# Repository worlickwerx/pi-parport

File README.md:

## pi-parport

This is a Raspberry Pi HAT that implements a PC-style parallel port.
GPIO pins are organized as data, status, and control registers.
The HAT includes a buffer chip that converts from the GPIB 3V3 logic
to signals that conform to IEEE 1284.  A 26 pin IDC header on the
board connects to your DB25 connector.  A `parport-gpio` driver and
device tree overlay integrate the HAT with the Linux parport driver stack.

### Why?

I wanted to use a parallel port based cooled astronomy camera,
but preferred to use the compact and low-power Raspberry Pi
over a PC at the telescope.  Parallel ports are simple devices.
Why not build one?

### What works?

See [wiki](https://github.com/worlickwerx/pi-parport/wiki) for notes on some
devices, and please share your experience if you try something new.

The following limitations of this implementation may affect software and
hardware that uses the parallel port:
1) The software cannot directly read and write the x86 port addresses,
as was the custom early on.  In user space, software must use the ppdev
ioctl interface.  In the kernel, software must use the (generic)
`struct parport` operations.
2) The GPIO multiplexing/de-multiplexing and/or system call access may
impact the direct-access latency assumed by some bit-banged drivers.
On a Pi 3, user space code can toggle a parallel port line at about 250 kHz.
3) Bidirectional control pins are not currently supported, but bidirectional
data pins are supported.  There are alternatives to the current buffer chip
that would support this, but they require a slightly more complicated
circuit.

### Why not use a USB Parallel Port?

Many USB parallel port devices appear to Linux as a USB printer, bypassing
the parport driver stack.  If your application is a printer, go for it.

### Building the driver

For convenience, the generic parport code is duplicated in this repo,
since the Raspberry Pi Foundation does not ship the compiled modules
in the `raspberrypi-kernel` package (at least in old Raspbian
versions).  If you are intending to use a specific old version of
Raspbian, there is the shell script `get_parport_src.sh` to assist
you in getting the code from that particular version.

Clone this repo, then run the following with `${TOPDIR}` representing the
top level directory of the cloned repo:
```console
$ sudo apt install build-essential raspberrypi-kernel-headers
$ cd ${TOPDIR}/driver
$ make
make -C /lib/modules/4.19.75-v7+/build M=${TOPDIR}/driver modules
make[1]: Entering directory '/usr/src/linux-headers-4.19.75-v7+'
  CC [M]  ${TOPDIR}/driver/parport/share.o
  CC [M]  ${TOPDIR}/driver/parport/ieee1284.o
  CC [M]  ${TOPDIR}/driver/parport/ieee1284_ops.o
  CC [M]  ${TOPDIR}/driver/parport/procfs.o
  CC [M]  ${TOPDIR}/driver/parport/daisy.o
  CC [M]  ${TOPDIR}/driver/parport/probe.o
  LD [M]  ${TOPDIR}/driver/parport/parport.o
  CC [M]  ${TOPDIR}/driver/parport/lp.o
  CC [M]  ${TOPDIR}/driver/parport/ppdev.o
  CC [M]  ${TOPDIR}/driver/parport_gpio.o
  Building modules, stage 2.
  MODPOST 4 modules
  CC      ${TOPDIR}/driver/parport/lp.mod.o
  LD [M]  ${TOPDIR}/driver/parport/lp.ko
  CC      ${TOPDIR}/driver/parport/parport.mod.o
  LD [M]  ${TOPDIR}/driver/parport/parport.ko
  CC      ${TOPDIR}/driver/parport/ppdev.mod.o
  LD [M]  ${TOPDIR}/driver/parport/ppdev.ko
  CC      ${TOPDIR}/driver/parport_gpio.mod.o
  LD [M]  ${TOPDIR}/driver/parport_gpio.ko
make[1]: Leaving directory '/usr/src/linux-headers-4.19.75-v7+'
```

### Installing the Device Tree Overlay

The device tree overlay maps specific GPIO pins to their functions in
the driver.  This must be compiled and loaded:
```console
$ cd ${TOPDIR}/dts
$ make
$ sudo make install
```
The ID EEPROM stores the name of the DT Overlay to use, and the
corresponding DT Overlay will be automatically loaded on boot.  If you
will not be using an ID EEPROM, then add the following line to
`/boot/config.txt`:
```
dtoverlay=parport-gpio
```
The default drive mode of the parallel port output pins is
"totem-pole" mode, which means that a high current source is provided
for both logic level 1 and 0.  If you wish logic level 1 to be a low
current source provided by pull-up resistors, i.e. "open-drain" mode,
then you can set the following DT Overlay parameter:
```
dtoverlay=parport-gpio,hd=0
```
Note that if you are using an EEPROM, you will have to include the
full DT Overlay data within your EEPROM since you cannot simply
specify a parameter when loading by that method.

Then reboot the pi to pick up the new config.

### Installing the Modules

Install the modules to allow Linux Device Tree to automatically load
them.
```console
$ cd ${TOPDIR}/driver
$ sudo make install
```
Note that only the `parport` and `parport_gpio` base modules will
autoload, the `ppdev` and `lp` modules will still need to be specified
in `/etc/modules` or otherwise.  Also, note that you will need to
rebuild and reinstall the modules when you update your kernel version.

### Loading the Modules

If you did not install the modules, after rebooting, load the base
modules like this:
```console
$ cd ${TOPDIR}
$ sudo insmod driver/parport/parport.ko
$ sudo insmod driver/parport_gpio.ko
```
You'll see the port announce itself on the console:
```console
[4425200.988400] parport-gpio ppgpio@0: data on pins [22,23,24,10,25,9,8,11]
[4425200.988412] parport-gpio ppgpio@0: status on pins [18,17,4,3,2]
[4425200.988422] parport-gpio ppgpio@0: control on pins [26,19,6,13]
[4425200.988430] parport-gpio ppgpio@0: hd on pin 20
[4425200.988438] parport-gpio ppgpio@0: dir on pin 21
```
If you wish to set up a parallel printer:
```console
$ sudo insmod parport/lp.ko
```
If you wish to run user-space programs that use the parallel port:
```console
$ sudo insmod parport/ppdev.ko
```

### hardware

The latest hardware includes an ID EEPROM to conform with the
[Raspberry Pi HAT Specification](https://github.com/raspberrypi/hats),
and was designed with [KiCAD](https://www.kicad.org/).
As with the previous versions, the
[SN74LVC161284 19-bit bus interface with 3-state outputs](http://www.ti.com/product/SN74LVC161284) takes care of buffering and line conditioning.

Version 4 is shared on
[OSHPARK](https://oshpark.com/shared_projects/0Ioh20Gk).
See the [Bill of Materials](hardware/v4/BOM.md) for parts to place on
the board.

Populating the EEPROM and associated components on a board you're making
yourself is optional.

Check out the [test](test/) directory for some simple "smoke tests"
on your assembled pi-parport board before attaching your more
expensive equipment.

Schematics and design files for [previous versions](hardware/)
are still available for reference.

### Release

Share and enjoy!

#### Software License

SPDX-License-Identifier: GPL-2.0-or-later

#### Hardware License

SPDX-License-Identifier: CERN-OHL-1.2

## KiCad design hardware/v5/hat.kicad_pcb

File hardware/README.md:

### v4 hardware

v4 mainly corrects some minor flaws in the v3 design.  Bypass
capacitors are added, a few traces are rerouted to avoid passing under
resistors, and the footprints for the EEPROM resistors are changed
from 0603 to 0805.  Also, a few CAD-related inconsistencies were
fixed, like unclosed board outline and footprints not being consistent
between the schematic and board layout files.

[Schematic](v4/pi-parport.pdf) and [Bill of Materials](v4/BOM.md).

### v3 hardware

v3 adds an EEPROM to be a proper HAT.  It also converts the design files 
from Eagle to KiCad as a step to making additional board variations and 
modifications more accessible.  Unfortunately, bypass capacitors were 
left out of the redesign.

This board is shared on [OSHPARK](https://oshpark.com/shared_projects/gevwv2YP).
See also:  [Schematic](v3/pi-parport.pdf) and [Bill of Materials](v3/BOM.md).

### v2 hardware

v2 addresses the line termination and data direction limitations of v1,
using a single, purpose-built chip, the
[SN74LVC161284 19-bit bus interface with 3-state outputs](http://www.ti.com/product/SN74LVC161284).

This board was designed with Eagle, and is shared on
[OSHPARK](https://oshpark.com/shared_projects/Padn3qhP).
See also: [Schematic](v2/schematic.pdf) and [Bill of Materials](v2/BOM.md).

It works!  However, it doesn't conform to the HAT specification because
of the lack of EEPROM, and the IDC connector footprint is for a vertical
connector, but right angle would have helped the Pi fit into smaller cases.
(RA works, but it hangs over the board edge).

### v1 hardware

Three
[74AHCT541 octal buffers/drivers with 3-state outputs](http://www.ti.com/product/SN74AHCT541)
chips convert to/from the Pi's 3V3 line level and the parallel port's 5V.

This board was designed with Eagle.  See also: [Schematic](v1/schematic.pdf).

This version worked for my intended application (SBIG parallel port camera),
but due to missing line termination, only with a very short cable.  This
design also does not implement bidirectional DATA.

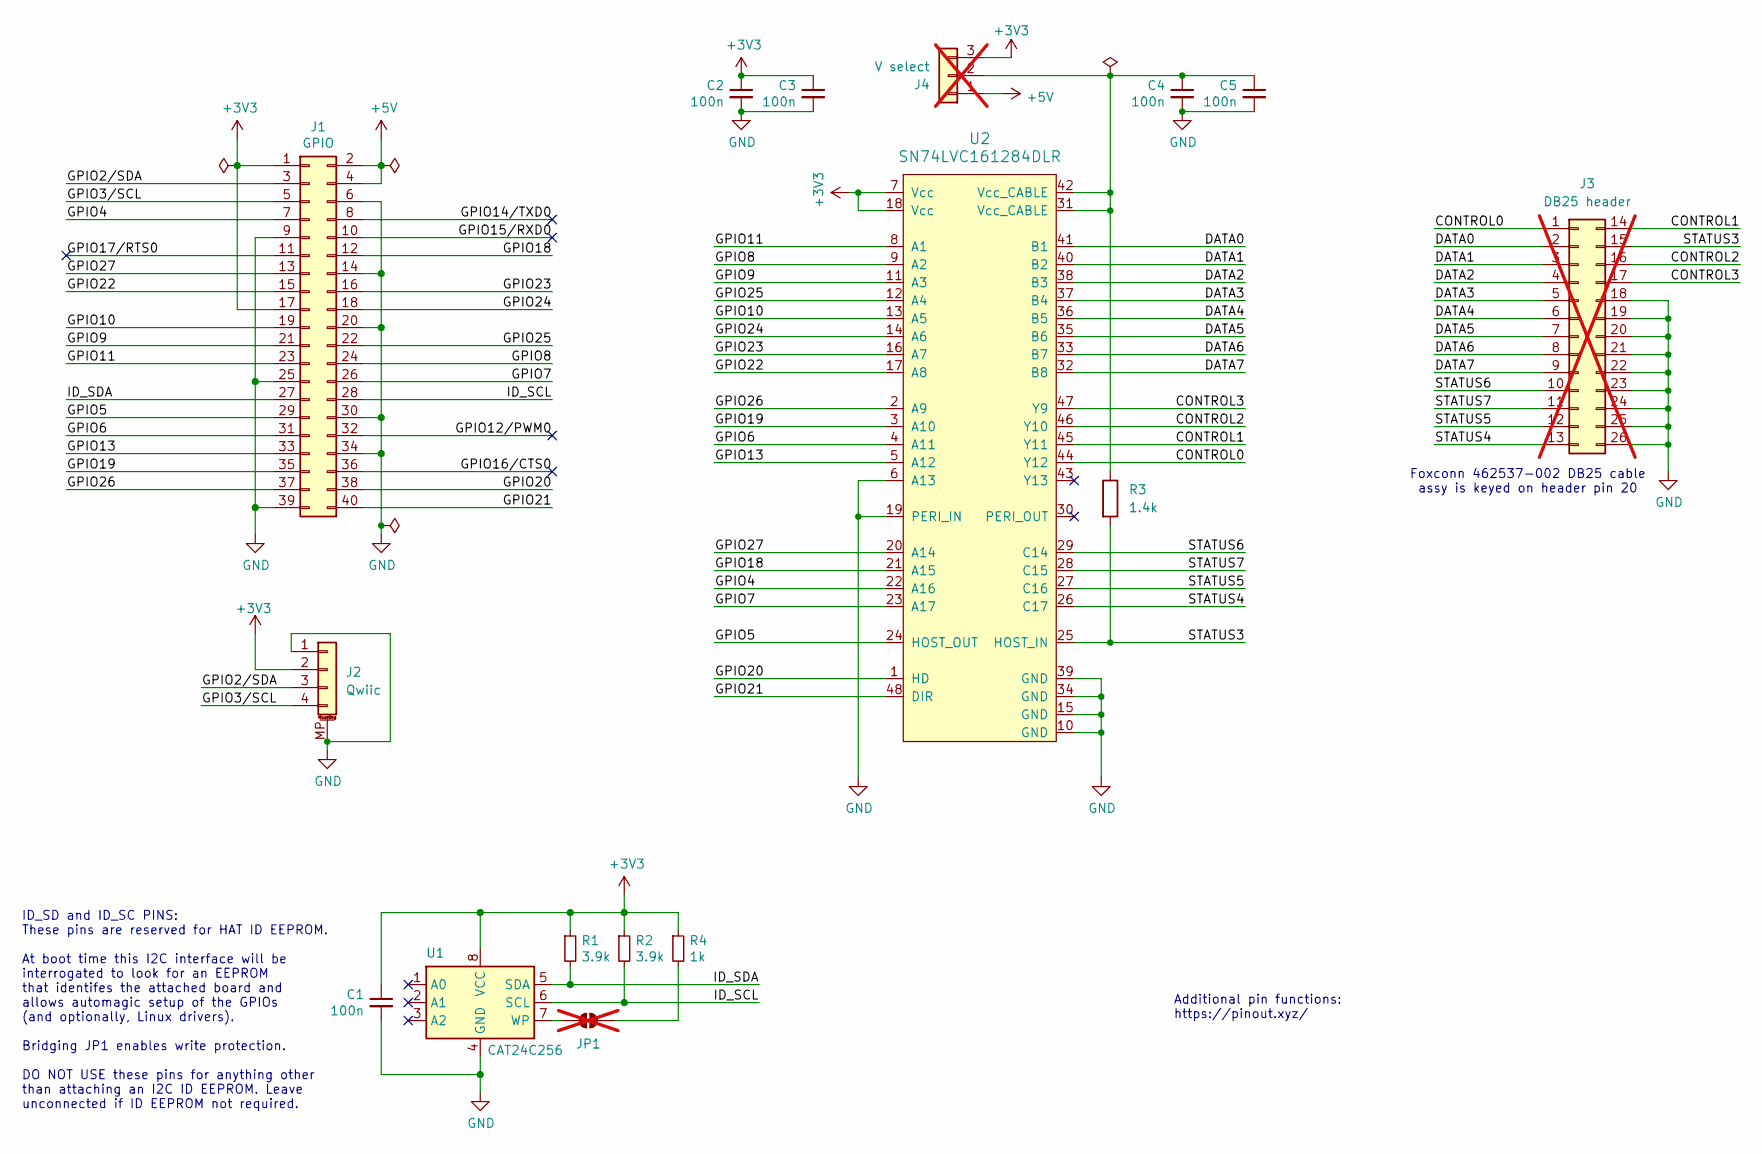
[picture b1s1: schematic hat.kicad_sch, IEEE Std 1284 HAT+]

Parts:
C1, C2, C3, C4, C5: 100n; C_0603_1608Metric; LCSC C346189
J1: GPIO; Harwin_M20-7812045_2x20_P2.54mm_Vertical; LCSC C2685112
J2: Qwiic; JST_SH_SM04B-SRSS-TB_1x04-1MP_P1.00mm_Horizontal; LCSC C2845363
J3: DB25 header; DB25_header_2x13_P2.54mm_horizontal; not fitted
J4: V select; PinHeader_1x03_P2.54mm_Vertical; not fitted
JP1: ID_WP; SolderJumper-2_P1.3mm_Open_RoundedPad1.0x1.5mm; not fitted
R1, R2: 3.9k; R_0603_1608Metric; LCSC C114616
R3: 1.4k; R_0603_1608Metric; LCSC C185359
R4: 1k; R_0603_1608Metric; LCSC C21190
U1: CAT24C256; SOIC-8_3.9x4.9mm_P1.27mm; LCSC C79987
U2: SN74LVC161284DLR; SSOP-48_7.5x15.9mm_P0.635mm; Mouser 595-SN74LVC161284DLR

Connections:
+3V3: C1.1, C2.1, C3.1, J1.1, J1.17, J2.2, J4.3, R1.1, R2.1, R4.1, U1.8 (VCC), U2.7 (Vcc), U2.18 (Vcc)
+5V: J1.2, J1.4, J4.1
/CONTROL0: J3.1, U2.44 (Y12)
/CONTROL1: J3.14, U2.45 (Y11)
/CONTROL2: J3.16, U2.46 (Y10)
/CONTROL3: J3.17, U2.47 (Y9)
/DATA0: J3.2, U2.41 (B1)
/DATA1: J3.3, U2.40 (B2)
/DATA2: J3.4, U2.38 (B3)
/DATA3: J3.5, U2.37 (B4)
/DATA4: J3.6, U2.36 (B5)
/DATA5: J3.7, U2.35 (B6)
/DATA6: J3.8, U2.33 (B7)
/DATA7: J3.9, U2.32 (B8)
/GPIO2/SDA: J1.3, J2.3
/GPIO3/SCL: J1.5, J2.4
/GPIO4: J1.7, U2.22 (A16)
/GPIO5: J1.29, U2.24 (HOST_OUT)
/GPIO6: J1.31, U2.4 (A11)
/GPIO7: J1.26, U2.23 (A17)
/GPIO8: J1.24, U2.9 (A2)
/GPIO9: J1.21, U2.11 (A3)
/GPIO10: J1.19, U2.13 (A5)
/GPIO11: J1.23, U2.8 (A1)
/GPIO12/PWM0: J1.32
/GPIO13: J1.33, U2.5 (A12)
/GPIO14/TXD0: J1.8
/GPIO15/RXD0: J1.10
/GPIO16/CTS0: J1.36
/GPIO17/RTS0: J1.11
/GPIO18: J1.12, U2.21 (A15)
/GPIO19: J1.35, U2.3 (A10)
/GPIO20: J1.38, U2.1 (HD)
/GPIO21: J1.40, U2.48 (DIR)
/GPIO22: J1.15, U2.17 (A8)
/GPIO23: J1.16, U2.16 (A7)
/GPIO24: J1.18, U2.14 (A6)
/GPIO25: J1.22, U2.12 (A4)
/GPIO26: J1.37, U2.2 (A9)
/GPIO27: J1.13, U2.20 (A14)
/ID_SCL: J1.28, R2.2, U1.6 (SCL)
/ID_SDA: J1.27, R1.2, U1.5 (SDA)
/STATUS3: J3.15, R3.2, U2.25 (HOST_IN)
/STATUS4: J3.13, U2.26 (C17)
/STATUS5: J3.12, U2.27 (C16)
/STATUS6: J3.10, U2.29 (C14)
/STATUS7: J3.11, U2.28 (C15)
GND: C1.2, C2.2, C3.2, C4.2, C5.2, J1.6, J1.9, J1.14, J1.20, J1.25, J1.30, J1.34, J1.39, J2.1, J2.MP (MountPin), J3.18, J3.19, J3.20, J3.21, J3.22, J3.23, J3.24, J3.25, J3.26, U1.4 (GND), U2.6 (A13), U2.10 (GND), U2.15 (GND), U2.19 (PERI_IN), U2.34 (GND), U2.39 (GND)
unnamed: C4.1, C5.1, J4.2, R3.1, U2.31 (Vcc_CABLE), U2.42 (Vcc_CABLE)
unnamed: JP1.1 (A), U1.7 (WP)
unnamed: JP1.2 (B), R4.2

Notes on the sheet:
Additional pin functions: https://pinout.xyz/
ID_SD and ID_SC PINS: These pins are reserved for HAT ID EEPROM. At boot time this I2C interface will be interrogated to look for an EEPROM that identifes the attached board and allows automagic setup of the GPIOs (and optionally, Linux drivers). Bridging JP1 enables write protection. DO NOT USE th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
Foxconn 462537-002 DB25 cable assy is keyed on header pin 20

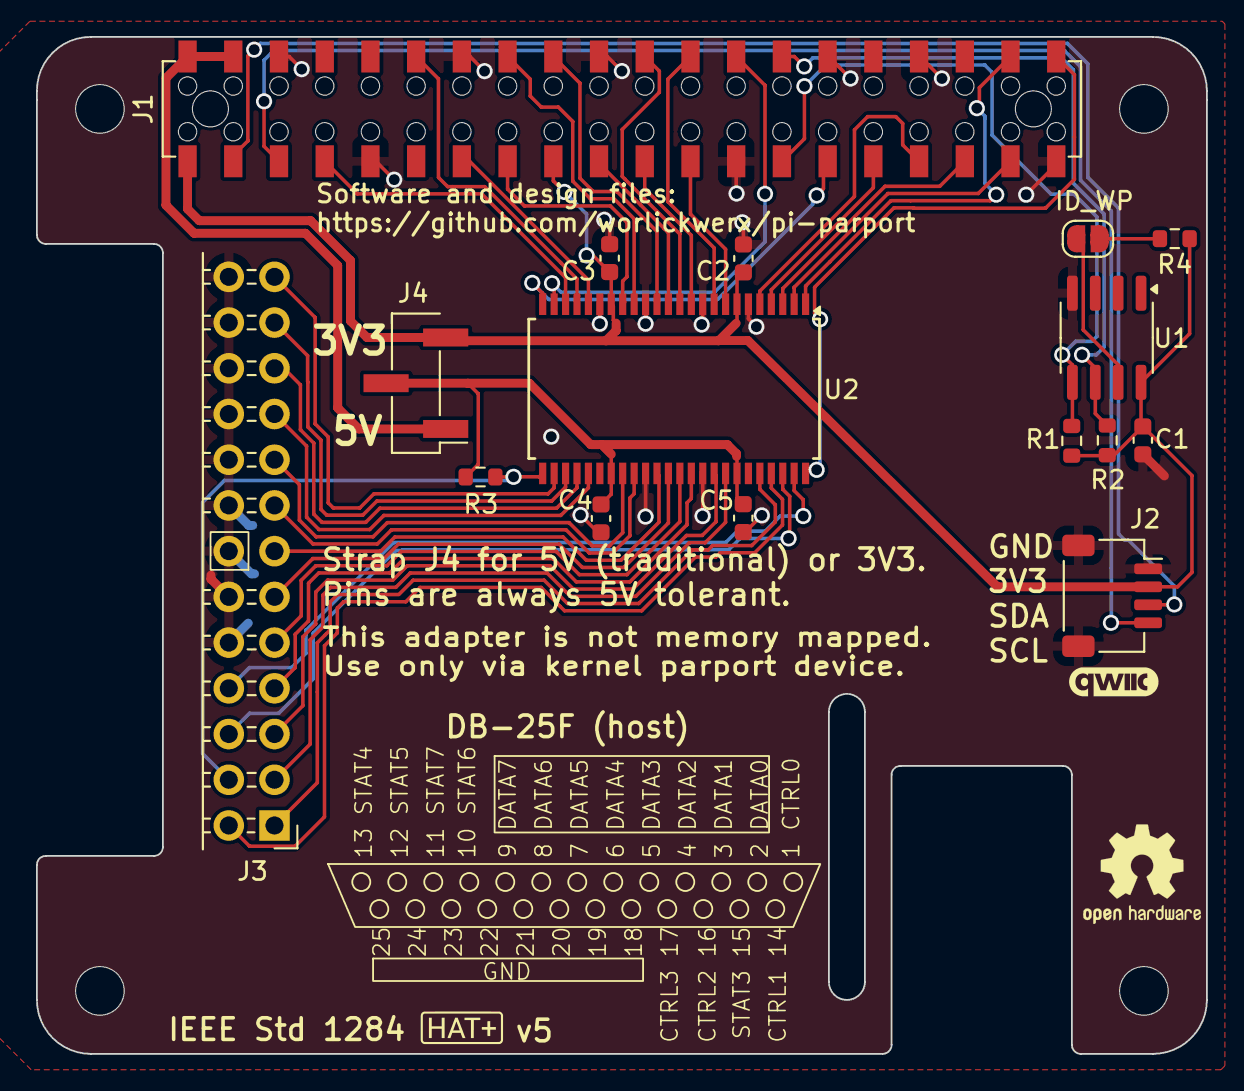
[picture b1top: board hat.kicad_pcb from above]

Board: 2 copper layers, 65.0 x 56.5 mm, 20 parts (0 on the bottom side), 46 nets.

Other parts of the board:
MH1, MH2, MH3, MH4: MountingHole_2.7mm_M2.5

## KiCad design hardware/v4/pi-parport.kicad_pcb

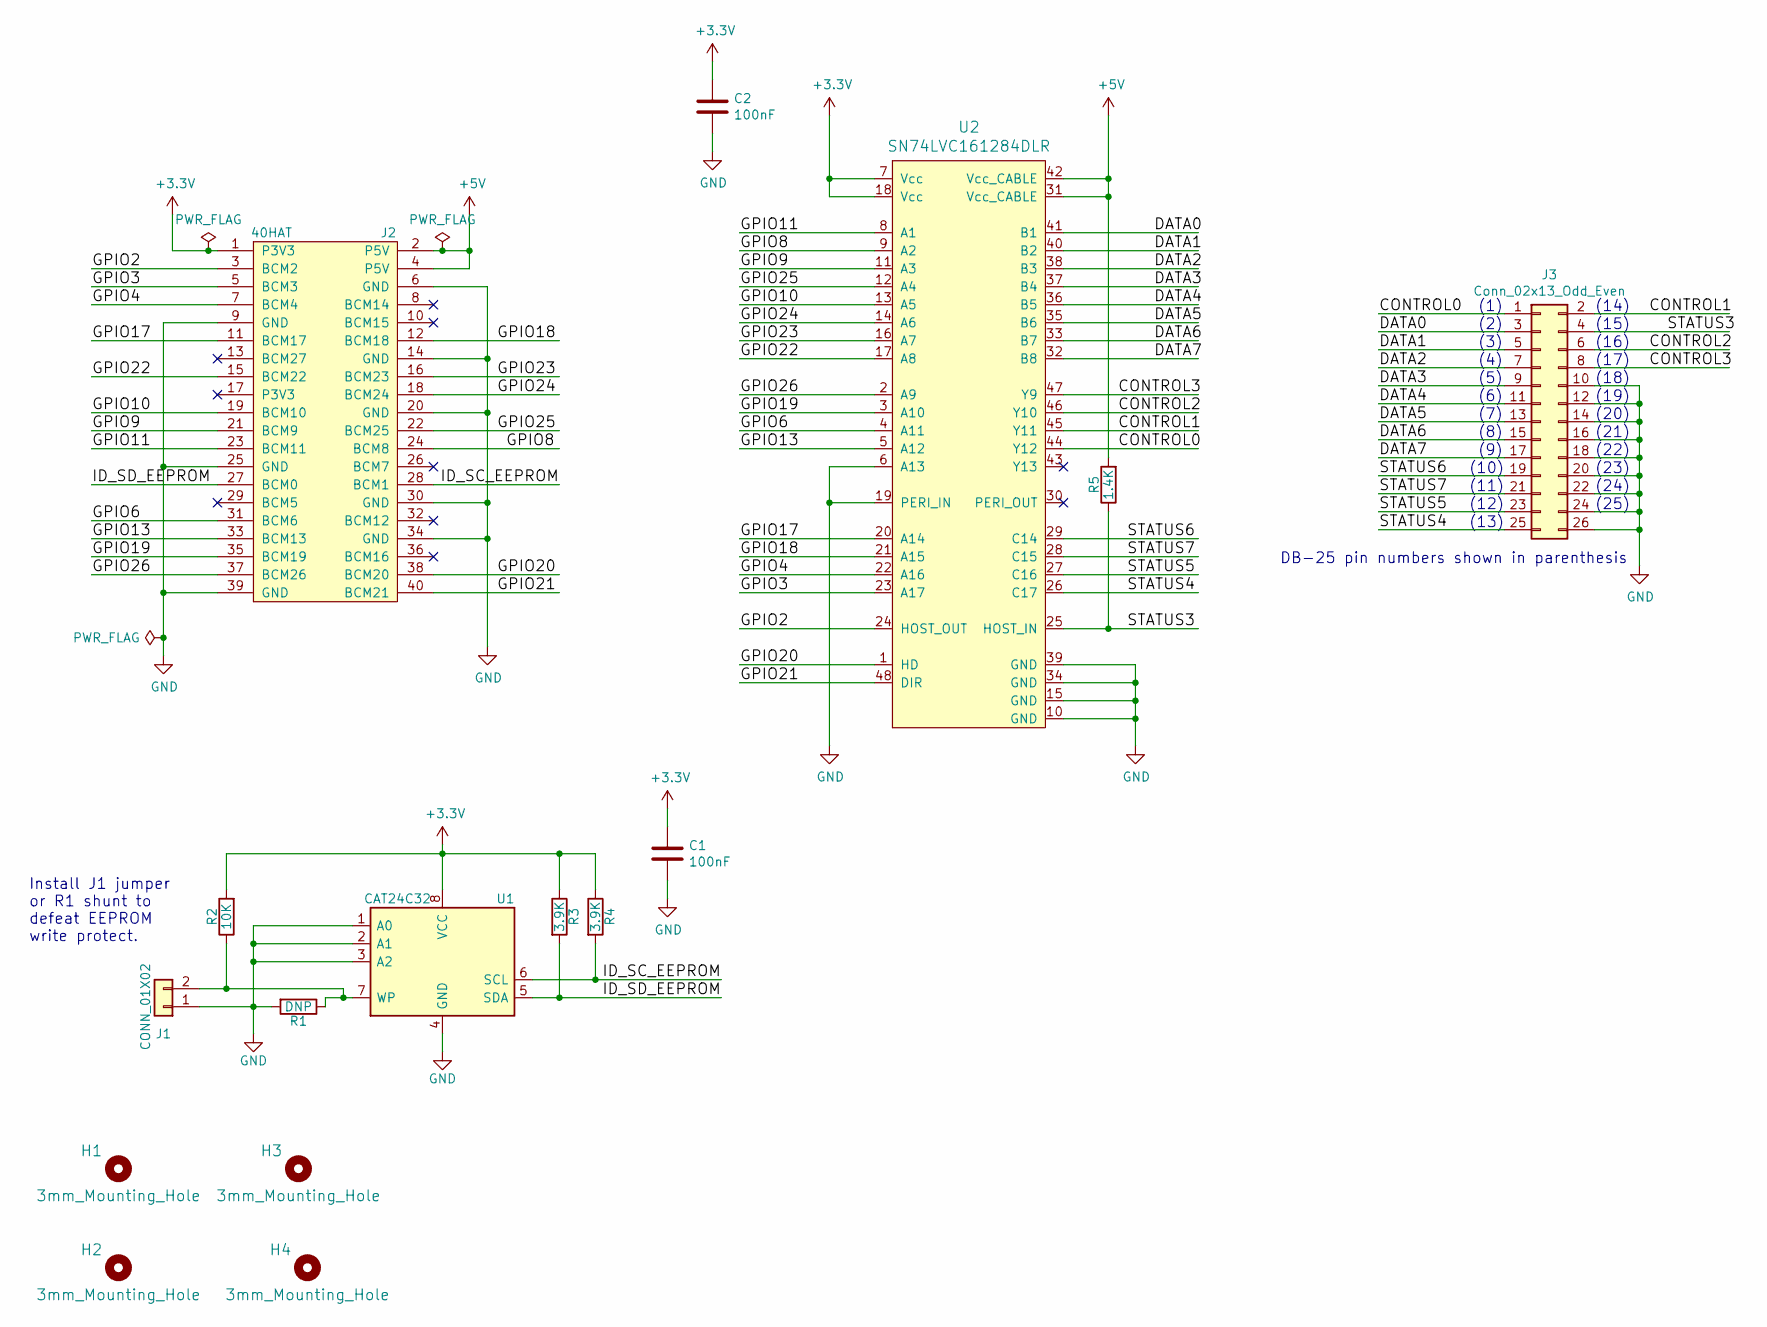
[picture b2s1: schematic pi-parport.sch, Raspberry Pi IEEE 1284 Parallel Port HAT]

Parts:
C1, C2: 100nF; C_0805_2012Metric_Pad1.15x1.40mm_HandSolder; MPN C0805C104Z5VACTU; Digi-Key_PN 399-1177-1-ND
H1, H2, H3, H4: 3mm_Mounting_Hole; NPTH_3mm_ID
J1: CONN_01X02; PinHeader_1x02_P2.54mm_Vertical; MPN M20-9990246; Digi-Key_PN 952-2262-ND
J2: 40HAT; PinSocket_2x20_P2.54mm_Vertical; MPN NPPN202AFCN-RC; Digi-Key_PN S5750-20-ND
J3: Conn_02x13_Odd_Even; PinHeader_2x13_P2.54mm_Horizontal; MPN 0877602616; Digi-Key_PN 23-0877602616-ND
R1: DNP; R_0805_2012Metric_Pad1.15x1.40mm_HandSolder
R2: 10K; R_0805_2012Metric_Pad1.15x1.40mm_HandSolder; MPN ERJ-6ENF1002V; Digi-Key_PN P10.0KCCT-ND
R3, R4: 3.9K; R_0805_2012Metric_Pad1.15x1.40mm_HandSolder; MPN ERJ-6ENF3901V; Digi-Key_PN P3.90KCCT-ND
R5: 1.4K; R_0805_2012Metric_Pad1.15x1.40mm_HandSolder; MPN ERJ-6ENF1401V; Digi-Key_PN P1.40KCCT-ND
U1: CAT24C32; SOIC-8_3.9x4.9mm_P1.27mm; MPN CAT24C32WI-GT3; Digi-Key_PN CAT24C32WI-GT3CT-ND
U2: SN74LVC161284DLR; SSOP-48_7.5x15.9mm_P0.635mm; MPN SN74LVC161284DLR; Digi-Key_PN 296-8467-1-ND

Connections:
+3V3: C1.1, C2.1, J2.1 (P3V3), R2.2, R3.1, R4.1, U1.8 (VCC), U2.7 (Vcc), U2.18 (Vcc)
+5V: J2.2 (P5V), J2.4 (P5V), R5.2, U2.31 (Vcc_CABLE), U2.42 (Vcc_CABLE)
/CONTROL0: J3.1, U2.44 (Y12)
/CONTROL1: J3.2, U2.45 (Y11)
/CONTROL2: J3.6, U2.46 (Y10)
/CONTROL3: J3.8, U2.47 (Y9)
/DATA0: J3.3, U2.41 (B1)
/DATA1: J3.5, U2.40 (B2)
/DATA2: J3.7, U2.38 (B3)
/DATA3: J3.9, U2.37 (B4)
/DATA4: J3.11, U2.36 (B5)
/DATA5: J3.13, U2.35 (B6)
/DATA6: J3.15, U2.33 (B7)
/DATA7: J3.17, U2.32 (B8)
/GPIO2: J2.3 (BCM2), U2.24 (HOST_OUT)
/GPIO3: J2.5 (BCM3), U2.23 (A17)
/GPIO4: J2.7 (BCM4), U2.22 (A16)
/GPIO6: J2.31 (BCM6), U2.4 (A11)
/GPIO8: J2.24 (BCM8), U2.9 (A2)
/GPIO9: J2.21 (BCM9), U2.11 (A3)
/GPIO10: J2.19 (BCM10), U2.13 (A5)
/GPIO11: J2.23 (BCM11), U2.8 (A1)
/GPIO13: J2.33 (BCM13), U2.5 (A12)
/GPIO17: J2.11 (BCM17), U2.20 (A14)
/GPIO18: J2.12 (BCM18), U2.21 (A15)
/GPIO19: J2.35 (BCM19), U2.3 (A10)
/GPIO20: J2.38 (BCM20), U2.1 (HD)
/GPIO21: J2.40 (BCM21), U2.48 (DIR)
/GPIO22: J2.15 (BCM22), U2.17 (A8)
/GPIO23: J2.16 (BCM23), U2.16 (A7)
/GPIO24: J2.18 (BCM24), U2.14 (A6)
/GPIO25: J2.22 (BCM25), U2.12 (A4)
/GPIO26: J2.37 (BCM26), U2.2 (A9)
/ID_SC_EEPROM: J2.28 (BCM1), R4.2, U1.6 (SCL)
/ID_SD_EEPROM: J2.27 (BCM0), R3.2, U1.5 (SDA)
/STATUS3: J3.4, R5.1, U2.25 (HOST_IN)
/STATUS4: J3.25, U2.26 (C17)
/STATUS5: J3.23, U2.27 (C16)
/STATUS6: J3.19, U2.29 (C14)
/STATUS7: J3.21, U2.28 (C15)
GND: C1.2, C2.2, J1.1, J2.6 (GND), J2.9 (GND), J2.14 (GND), J2.20 (GND), J2.25 (GND), J2.30 (GND), J2.34 (GND), J2.39 (GND), J3.10, J3.12, J3.14, J3.16, J3.18, J3.20, J3.22, J3.24, J3.26, R1.2, U1.1 (A0), U1.2 (A1), U1.3 (A2), U1.4 (GND), U2.6 (A13), U2.10 (GND), U2.15 (GND), U2.19 (PERI_IN), U2.34 (GND), U2.39 (GND)
unnamed: J1.2, R1.1, R2.1, U1.7 (WP)

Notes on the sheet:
(1)
(2)
(3)
(4)
(5)
(6)
(7)
(8)
(9)
(10)
(11)
(12)
(13)
(14)
(15)
(16)
(17)
(18)
(19)
(20)
(21)
(22)
(23)
(24)
(25)
DB-25 pin numbers shown in parenthesis
Install J1 jumper or R1 shunt to defeat EEPROM write protect.

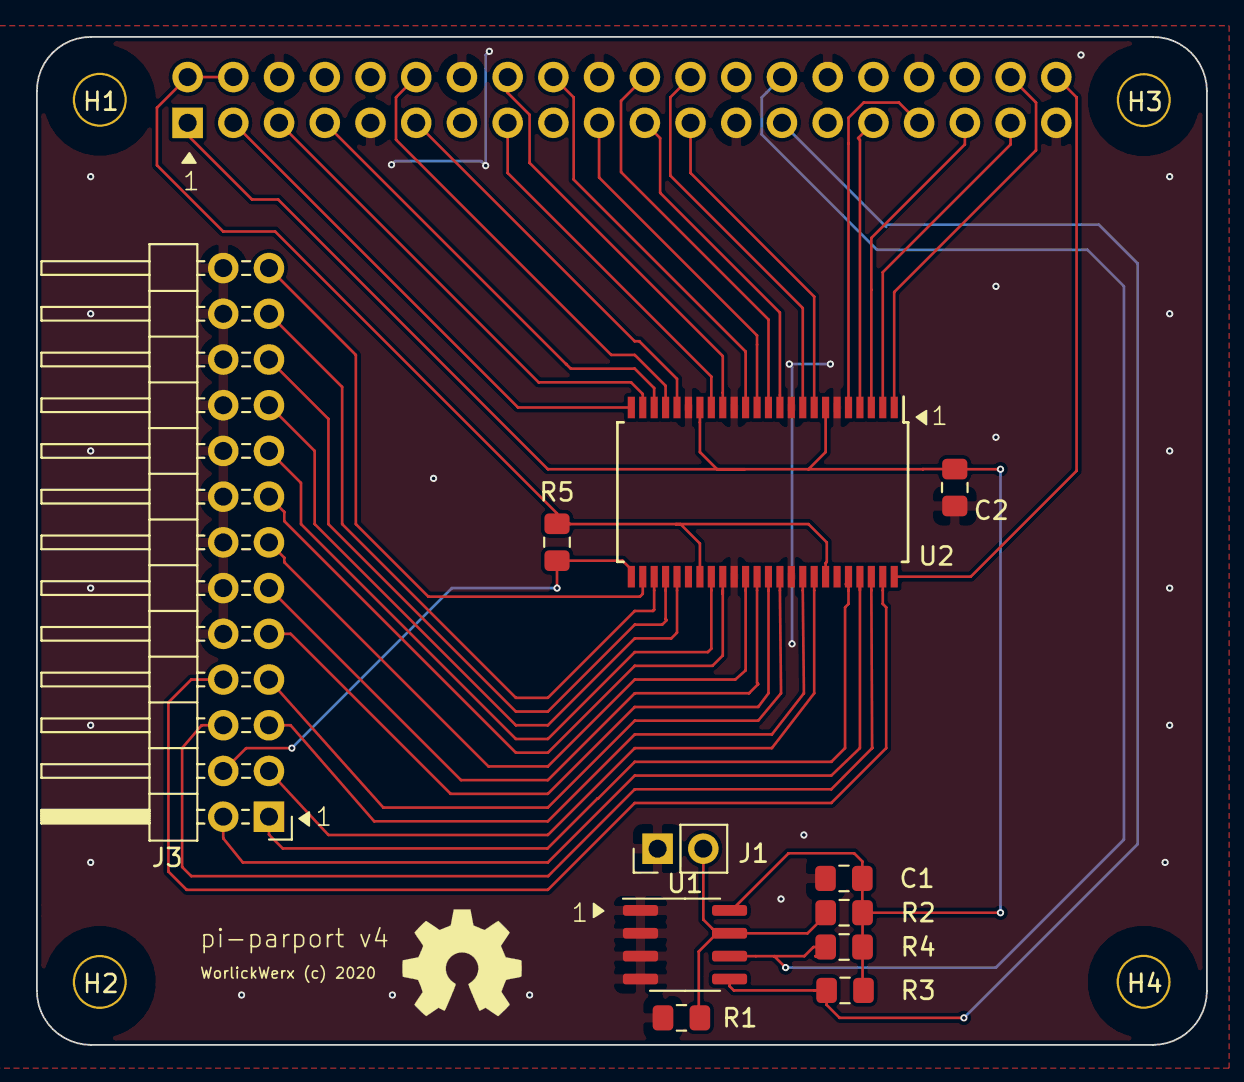
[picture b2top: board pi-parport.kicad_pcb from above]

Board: 2 copper layers, 65.0 x 56.0 mm, 16 parts (1 on the bottom side), 42 nets.

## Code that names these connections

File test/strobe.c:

// SPDX-License-Identifier: GPL-2.0-or-later

/* strobe - pulse specified pin for scope */

#include <stdio.h>
#include <sys/ioctl.h>
#include <linux/parport.h>
#include <linux/ppdev.h>
#include <fcntl.h>
#include <time.h>
#include <unistd.h>
#include <stdlib.h>
#include <stdarg.h>
#include <errno.h>
#include <string.h>

#define DEVICE_PATH "/dev/parport0"

void die (const char *fmt, ...)
{
    va_list ap;

    va_start (ap, fmt);
    (void)vfprintf (stderr, fmt, ap);
    va_end (ap);
    exit (1);
}

void say (const char *fmt, ...)
{
    va_list ap;

    va_start (ap, fmt);
    (void)vfprintf (stderr, fmt, ap);
    va_end (ap);
}

void usage (void)
{
    fprintf (stderr, "Usage: strobe pin\n");
    fprintf (stderr, "where pin is DATA0, DATA1, CONTROL0, CONTROL1...\n");
    exit (1);
}

/* measured 253khz in a tight loop on pi3 */
void strobe (int fd, const char *pin)
{
    unsigned char out;
    unsigned long request;
    int bit;
    int count;

    if (!strncmp (pin, "DATA", 4)) {
        bit = atoi (pin + 4);
        if (bit < 0 || bit > 7)
            usage ();
        request = PPWDATA;
    }
    else if (!strncmp (pin, "CONTROL", 7)) {
        bit = atoi (pin + 7);
        if (bit < 0 || bit > 4)
            usage ();
        request = PPFCONTROL;
    }
    else
        usage ();

    for (count = 0; ; count++) {
        if (request == PPWDATA) {
            unsigned char out = (count % 2) ? 0 : (1<<bit);

            if (ioctl (fd, request, &out) < 0)
                die ("ioctl PPWDATA: %s\n", strerror (errno));
        }
        else {
            struct ppdev_frob_struct frob = {
                .mask = 1<<bit,
                .val = (count % 2) ? 0 : (1<<bit),
            };
            if (ioctl (fd, request, &frob) < 0)
                die ("ioctl PPFCONTROL: %s\n", strerror (errno));
        }
    }
}

int main (int argc, char *argv[])
{
    int fd, mode, dir;
    const char *pin;
    int rc;

    if (argc != 2)
        usage ();
    pin = argv[1];

    fd = open (DEVICE_PATH, O_RDWR);
    if (fd < 0)
        die ("%s: %s\n", DEVICE_PATH, strerror (errno));
    if (ioctl (fd, PPCLAIM, NULL) < 0)
        die ("ioctl PPCLAIM: %s\n", strerror (errno));

    mode = IEEE1284_MODE_BYTE;
    if (ioctl (fd, PPSETMODE, &mode) < 0)
        die ("ioctl PPSETMODE IEEE1284_MODE_BYTE: %s\n", strerror (errno));

    dir = 0;
    if (ioctl (fd, PPDATADIR, &dir) < 0)
        die ("ioctl PPDATADIR 0 (out): %s\n", strerror (errno));

    strobe (fd, pin);

    if (ioctl (fd, PPRELEASE) < 0)
        die ("ioctl PPRELEASE: %s\n", strerror (errno));
    if (close(fd) < 0)
        die ("close %s: %s\n", DEVICE_PATH, strerror (errno));

   return rc;
}

/*
 * vi:tabstop=4 shiftwidth=4 expandtab
 */

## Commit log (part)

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2017-06-25 hardware_v1: add initial prototype hardware
    This is a pi HAT (not officially: no EEPROM, wrong size) that
    has a DB25 on it and three 74AHCT541 8-channel buffers for
    3V3/5V level conversion. Pi GPIOs are mapped directly to
    parallel port data, status, and control lines. It should be
    adequate for SPP mode.
    It's layed out as a single sided board since that's easier for
2017-06-25 README: add project readme
2017-07-30 dts: add device tree overlay
    Add initial device tree overlay for parport-gpio module
    to identify and provide initial config for GPIO pins assigned
    to data, status, and control ports.
    The "compatible" name links the driver and the dts file.
    On the pi, after the compiled dtbo file is installed,
    add the following to /boot/config.txt:
2017-07-30 driver: pull in the rest of the parport stack
    Since the Pi Foundation isn't likely to configure the parport
    stack in their default kernel anytime soon, pull in the bits
    here so they can be built out of tree with the parport-gpio
    module, thus making it a bit easier to get started.
    insmod parport.ko
    insmod parport_gpio.ko
2017-08-05 hardware_v1: status 10k pd -> 4.3k pu
    Change the 10K pulldowns to 4.3K pullups.
    4.7K is what would normally be used here but I had some
    803 4.3K's on hand.
    Place some vias for the pullups and also for the unrouted
    CONTROL3 line. Before we had a one sided board which is
    a bit easier to fab with the CNC. Place vias so it can
2017-08-06 hardware_v1: include DB-25 pin numbering on schematic
2017-08-06 driver: fix NULL oops
    If CONFIG_PARPORT_NOT_PC is not defined and CONFIG_PARPORT_1284
    is defined, internal 1284 "daisy" probing causes a NULL pointer
    dereference (oops) at insmod of parport_gpio.ko.
    This is likely due to a conditional in parport.h that, if NOT_PC
    is undefined, hardwires operations to the PC versions, bypassing
    the operations table. I did not run down why the hardwired
2017-08-06 README.md: fix typos
2017-08-06 driver: delete port on module unload
    Call parport_del_port() instead of parport_put_port()
    when the module is unloaded, so that parport0 can be
    reused if the module is re-loaded. Otherwise we get
    parport1, 2, and so on.
    Also, change printk code so the port number is displayed
    with the assigned GPIO pins e.g.
2017-08-06 driver: fix polarity in parport_gpio_read_control()
    In parport_gpio_read_control(), it is necessary to invert
    some of the control bits that are supposed to be active low.
2017-08-06 driver: optimize frob_control operation
    Write bits individually if present in the mask rather than
    doing it in bulk as if we were dealing with actual I/O ports.
    Fixes #5
2017-08-06 README.md: note the upstream code pulled in
2017-08-07 driver: stop using raw gpiod interface
    In the dts file expression <&gpio n m>, n is the pin and m
    is the polarity, not direction. If m=0, the pin is active
    high; if m=1, active low.
    Set all the pins active high and then stop using
    the "raw" gpiod interfaces to access them.
    Fixes #3
2017-08-13 dts: [cosmetic] fix comments and formatting
2017-08-24 test/cableTest2: add simple ppdev based cable test
    Add a simple parallel port cable test that toggles
    the data lines from user space via ppdev.
    Credit: Dr. Andrew Greensted
    http://www.labbookpages.co.uk/electronics/parallelPort.html
2017-10-22 hardware_v2: add pdfs
2017-10-22 hardware_v2: fix drc errors, add silk title
    This version ordered from OSH Park (3 boards).
2017-12-04 driver: support hd and dir pins for v2 hardware
    In the v2 hardware design, hd and dir are pins on the
    SN74LVC161284 19-bit bus interface that determine the
    drive mode (1=totem pole, 0=open drain) and data port
    direction (1=AtoB, 0=BtoA).
    If the device tree overlay defines them, initialize
    both pins to 1.
2017-12-08 test/loop: add loopback test
2018-07-09 driver: update some includes
    Problem: compilation errors with latest rpi kernel
    headers (1.20180703-1), in generic parport, ppdev, lp code.
    This really should be synced with upstream kernel sources,
    but an initial check didn't reveal any changes to the parport
    stuff. For now, adjust includes to avoid compilation errors.
2018-07-11 README.md: add oshpark link
2018-09-09 hardware_v2: add bill of materials
2019-04-27 driver/parport: move upstream copies to parport dir
    Problem: parport module code that the rpi foundation doesn't
    configure into their kernel, but which is required by parport-gpio,
    was copied into our repo. But it's not clear what's the new code
    and what's copied kernel code.
    Move the copied kernel code into the parport subdir.
2019-04-27 driver: [style] add missing blank line after decls
    Address checkpatch warning:
    WARNING: Missing a blank line after declarations
2019-04-27 driver: [style] drop extra oom message
    Address checkpatch warning:
    WARNING: Possible unnecessary 'out of memory' message
    See also: https://lkml.org/lkml/2014/6/10/382
2019-04-27 driver: [style] fix malformed SPDX-License-Identifier
    Address checkpatch warning:
    WARNING: Missing or malformed SPDX-License-Identifier tag in line 1
2019-04-27 driver: [style] reformat with clang-format
    Add .clang-format from source and run
    clang-format -i parport_gpio.c
    to automatically fix as many kernel style issues as
    possible in one go.
2019-04-27 driver: add make check target that runs checkpatch
    Run the kernel style checker in response to 'make check'.
2019-04-27 README.md: update console output
    Switching to the dev_{level} printk macros causes some
    minor changes in the expeced console output, so update
    the README.md example output.
2019-08-04 drivers/parport: update source to track raspbian
    Problem: parport code fails to compile after raspbian update
    to 4.19.57-v7+ kernel.
    Update parport code that we copied into this project from
    the kernel source, needed until pi kernel maintainers enable
    the parallel port code in their configuration (not very likely).
    Code copied from master branch of:
2020-01-02 hardware_v3: rework v2 in KiCAD
    Create a new hardware version with the following changes
    1) Use KiCAD instead of Eagle so that other people can
    more easily modify/remix.
    2) Add HAT EEPROM to conform to Pi Foundation specs
    3) OSHW logo on board
    After I sent this to OSHPARK I realized I omitted the
2020-01-02 hardware_v3: add schematic pdf
2020-01-02 test/loop: add second loopback pinout
    Call the ebay plug "Plug A".
    Refactor to allow the type of plug and the number of
    iterations to be specified on the command line.
    Add "Plug B" with pinout designed to cover pins not
    covere by "Plug A".
2020-01-02 test/walk: drop test
    With a second loopback plug, there is no longer any
    need for the "walk" test.
2020-01-02 test/loop: add SPDX license reference
2020-01-02 README.md: move old versions to hardware_old
2020-01-02 README.md: add OSHAPRK link
2020-01-03 eeprom: add notes and Makefile to flash EEPROM
    Verify that the EEPROM hardware works by flashing a
    board identity in there.
    Fixes #26
2020-03-12 hardware_v3: add BOM manufacturer part numbers
2020-03-12 hardware_v3: also add package, description, notes fields for BOM
2020-03-13 hardware_v3: fix BOM table heading
2020-06-20 driver: skip parport if KERNEL_HAS_PARPORT defined
2020-07-26 Rearrange hardware repo structure.
2020-07-26 hardware: add generated media
2020-07-26 hardware_v4: add bypass capacitors, reroute traces
    Do not route trace under resistor R5. Move U2 upward to facilitate
    rerouting this trace without adding more vias.
    Also make sure footprints between schematic and PCB are in sync.
    Update BOM with new parts.
    Hardware version needs to be bumped due to PCB changes. Version numbers
    in schematic and PCB source changed, new files will need to be generated
2020-07-26 hardware: no symlinks for Markdown images on GitHub
2020-08-11 hardware: BOM improvements/fixes.
    * Fix capacitor quantity in v4.
    * SN74LVC161284DLR Digi-Key part number: cut tape packaging
    discontinued at Digi-Key, use tube packaging instead.
    * Fix 40-pin and 26-pin headers, accidentally picked 2 mm pitch parts
    instead of 2.54 mm pitch parts.
2020-10-18 Update gpiod_set_array_value call to new contract.
2020-10-23 Correct error in README.md.
2020-10-23 driver: Forwards and backwards compatibility with Linux versions.
    Also make corresponding improvements to the READMEs.
    Fix a few checkpatch.pl warnings recently introduced, while at the same
    time introducing four checkpatch.pl warnings due to conditional
    compilation on the Linux version.
2020-11-01 Remove trailing whitespace accidentally added to README.md.
2020-11-11 dts, driver: Add DT Overlay parameter for drive mode.
2021-01-02 hardware: Add DIP jumper to BOM.
2021-01-05 README: point to v4 board + BOM, not v3
    Problem: the top level README.md still points to the v3 board
    on oshpark.
    Change it to point to the v4 board, and update the BOM reference
    to v4 as well.
2021-01-06 ci: add driver builds
    Add jobs to the main github workflow that install kernel headers
    and build the driver for:
    - Ubuntu 20.04 / linux 5.4.0
    - Ubuntu 18.04 / linux 4.15.0
    - Ubuntu 16.04 / linux 4.4.0
2021-01-06 ci: invoke pr-validator on PRs
    Add a 'main' github workflow containing one 'job',
    that validates PRs, ensuring that:
    - commit messages conform to line length recommendations
    - commit subjects don't include "fixup" or "squash"
    - there are no merge commits
    The validator script was shared from:
2021-11-12 ci: drop ubuntu-16.04 / linux-4.4 build
    Problem: CI workflow hangs waiting for nonexistent runner type.
    Github has deprecated the ubuntu-16.04 runner.
    Drop the ubuntu-16.04 / linux-4.4 build.
2021-11-12 ci: load the driver
    Problem: CI does not catch errors that occur when the
    driver is loaded.
    Add a test that builds the driver against the running kernel
    and loads it.
2021-11-14 driver/parport: sync with linux-5.10
    Problem: vendored copy of parport code no longer compiles
    on raspbian kernel 5.10.63-v7+ due to kernel API changes.
    Pull in the latest copy of parport source from linux-5.10.
    There are no local modifications.
2024-09-01 v5: update page settings
    Problem: template pages are A4 size and have have boiler plate
    metadata.
    Switch to U.S. letter size and update page metadata with project
    specific info.
2024-09-17 v5: import/reimplement parport design on template
    Problem: template board is still blank.
    Adjust board edge to handle SMT header and add cutout for pi5 camera/
    display FFC connectors. For GPIO connector, use existing kicad 8 Harwin
    M20 series footprint but adjust the pinout for top of board pi GPIO,
    and adjust position since centroid moved from THT pin 1 to SMT centroid.
    Add keepout for pi5 PoE like the existing one for pi4.
2024-09-21 ci: update checkout action to v4 to silence warnings
    Problem: github issues warnings when it runs our ci:
    The following actions uses node12 which is deprecated and will
    be forced to run on node16: actions/checkout@v2.
    Switch to v4.
2024-09-21 ci: add github action to check v5 ERC/DRC
    Problem: new PR's that change board design files should be
    automatically checked.
2024-09-22 build: add script to generate gerbers
    Problem: we need gerbers for the fab house.
    Add a script to generate gerbers as a zip file.
    Add a Makefile target for the v5 board.
2024-09-22 v5: add BOM data needed for JLCPCB assembly
    Problem: component metadata is not in a form that could be sent
    out for assembly.
    Add BOM fields recommended for JLCPCB assembly[1] and fill in.
    [1] https://jlcpcb.com/help/article/How-to-generate-the-BOM-and-Centroid-file-from-KiCAD
2024-09-22 build: add script to generate BOM csv file
    Problem: we need a csv file to send to the board assembly house.
    Add a script to generate it and a Makefile target for the v5 board.
2024-10-03 v5: enlarge 2x20 header alignment holes
    Problem: 2x20 header alignment holes for Harwin M20 are 1.8mm dia.
    The LCSC replacement requires 2mm dia alignment holes.
    Update footprint and board.
2024-10-03 v5: switch J4 to SMT
    Problem: the J4 1x3 header is a through hole part that is marked
    "do not place" so it can be installed by hand.
    Switch J4 to an SMT footprint and uncheck DNP.
    Adjust board routing.
    Add a LCSC part number to the BOM.
2024-10-04 v5: remove some DRC exclusions
    Problem: DCR excludes "holes inside courtyard" for some reason.
    These checks pass so may as well enable them.

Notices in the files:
hardware/v4/pi-parport.kicad_pcb:
WorlickWerx (c) 2020
hardware/v5/hat.kicad_pcb:
(C)2024 WorlickWerx, LLC
